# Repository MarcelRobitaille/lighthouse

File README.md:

# Lighthouse

> Lighthouse is a PCB that controls lights in my house.

## Features

- ESP8266 module (works with ESPHome)
- Two constant voltage outputs and two constant current outputs
- Powered from USB-C, barrel, or screw terminal
- Voltage outputs can be powered separately, or from global USB/barrel/screw terminal

It's doesn't have to be for lighting, but any small load you wish to switch remotely.

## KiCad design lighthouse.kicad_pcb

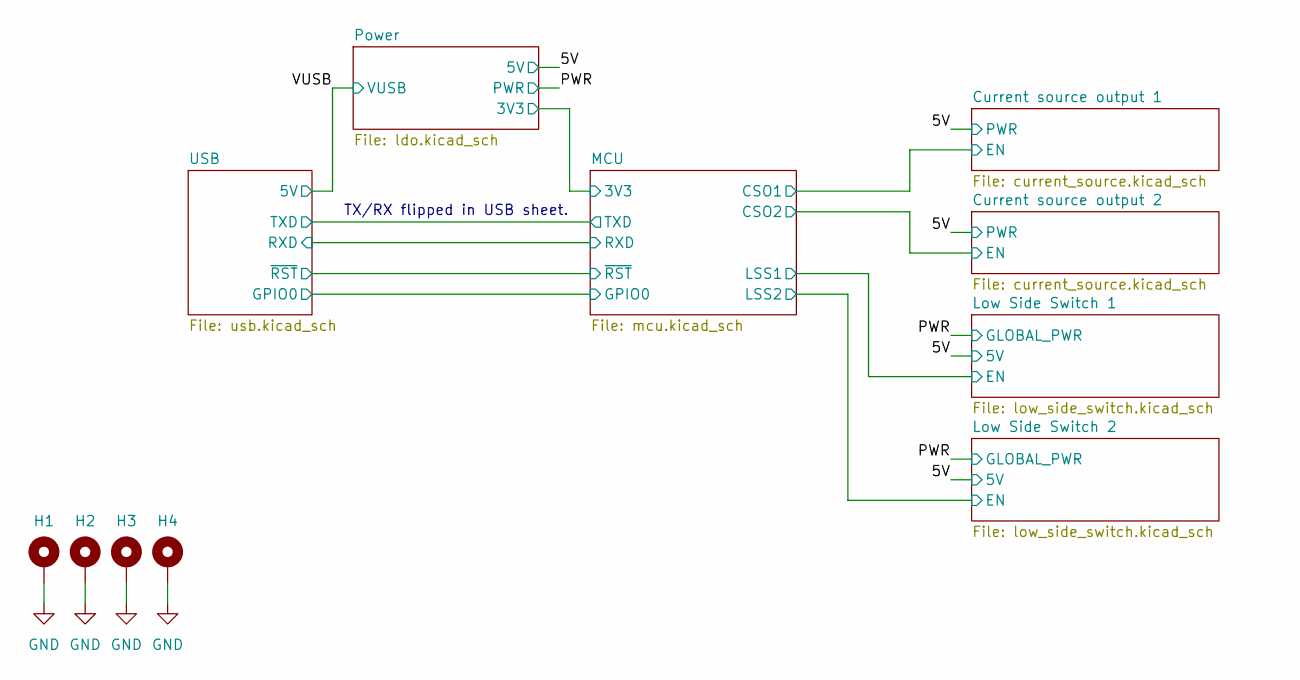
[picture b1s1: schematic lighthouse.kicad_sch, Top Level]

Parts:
H1, H2, H3, H4: MountingHole_Pad; MountingHole_2.2mm_M2_Pad

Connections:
GND: H1.1, H2.1, H3.1, H4.1; also elsewhere on the board

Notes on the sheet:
TX/RX flipped in USB sheet.

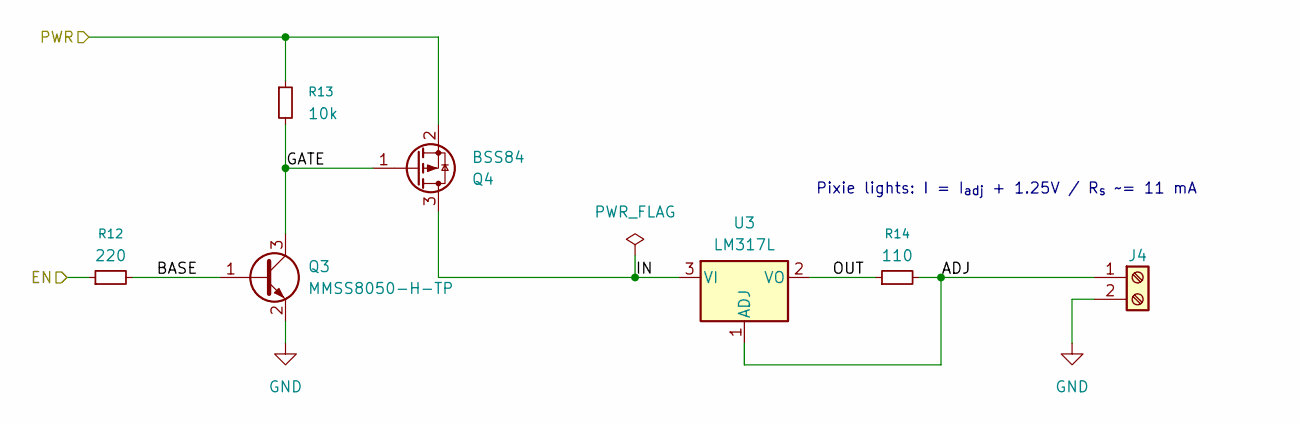
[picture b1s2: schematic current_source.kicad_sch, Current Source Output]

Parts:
J4: TB0010-500-02GR; TerminalBlock_TB0010-500-02GR_1x02_P5.00mm
Q3: MMSS8050-H-TP; SOT-23-3; MPN MMSS8050-H-TP; LCSC Part Number C2891804
Q4: BSS84; SOT-23; MPN BSS84PH6327XTSA2; Digikey Part Number BSS84PH6327XTSA2CT-ND
R12: 220; R_0805_2012Metric; MPN CRCW0805220RJNEA; Mouser Part Number 71-CRCW0805220RJNEA
R13: 10k; R_0805_2012Metric; Tolerance 5 %; MPN CRCW080510K0JNEAC; Mouser Part Number 71-CRCW080510K0JNEAC
R14: 110; R_0805_2012Metric; Tolerance 1%; MPN CRCW0805110RFKEA; Mouser Part Number 71-CRCW0805-110-E3
U3: LM317L; SOT-89-3; MPN LM317LCPK; Mouser Part Number 595-LM317LCPK

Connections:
/5V: Q4.2 (S), R13.1; also elsewhere on the board
/Current source output 2/ADJ: J4.1, R14.2, U3.1 (ADJ)
/Current source output 2/BASE: Q3.1 (B), R12.2
/Current source output 2/GATE: Q3.3 (C), Q4.1 (G), R13.2
/Current source output 2/IN: Q4.3 (D), U3.3 (VI)
/Current source output 2/OUT: R14.1, U3.2 (VO)
/MCU/CSO2: R12.1; also elsewhere on the board
GND: J4.2, Q3.2 (E); also elsewhere on the board

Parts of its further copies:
J7: TB0010-500-02GR; TerminalBlock_TB0010-500-02GR_1x02_P5.00mm
Q5: MMSS8050-H-TP; SOT-23-3; MPN MMSS8050-H-TP; LCSC Part Number C2891804
Q6: BSS84; SOT-23; MPN BSS84PH6327XTSA2; Digikey Part Number BSS84PH6327XTSA2CT-ND
R15: 220; R_0805_2012Metric; MPN CRCW0805220RJNEA; Mouser Part Number 71-CRCW0805220RJNEA
R16: 10k; R_0805_2012Metric; Tolerance 5 %; MPN CRCW080510K0JNEAC; Mouser Part Number 71-CRCW080510K0JNEAC
R17: 110; R_0805_2012Metric; Tolerance 1%; MPN CRCW0805110RFKEA; Mouser Part Number 71-CRCW0805-110-E3
U6: LM317L; SOT-89-3; MPN LM317LCPK; Mouser Part Number 595-LM317LCPK

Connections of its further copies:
/5V: Q6.2 (S), R16.1; also elsewhere on the board
/Current source output 1/ADJ: J7.1, R17.2, U6.1 (ADJ)
/Current source output 1/BASE: Q5.1 (B), R15.2
/Current source output 1/GATE: Q5.3 (C), Q6.1 (G), R16.2
/Current source output 1/IN: Q6.3 (D), U6.3 (VI)
/Current source output 1/OUT: R17.1, U6.2 (VO)
/MCU/CSO1: R15.1; also elsewhere on the board
GND: J7.2, Q5.2 (E); also elsewhere on the board

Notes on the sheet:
Pixie lights: I = I_{adj} + 1.25V / R_{s} ~= 11 mA

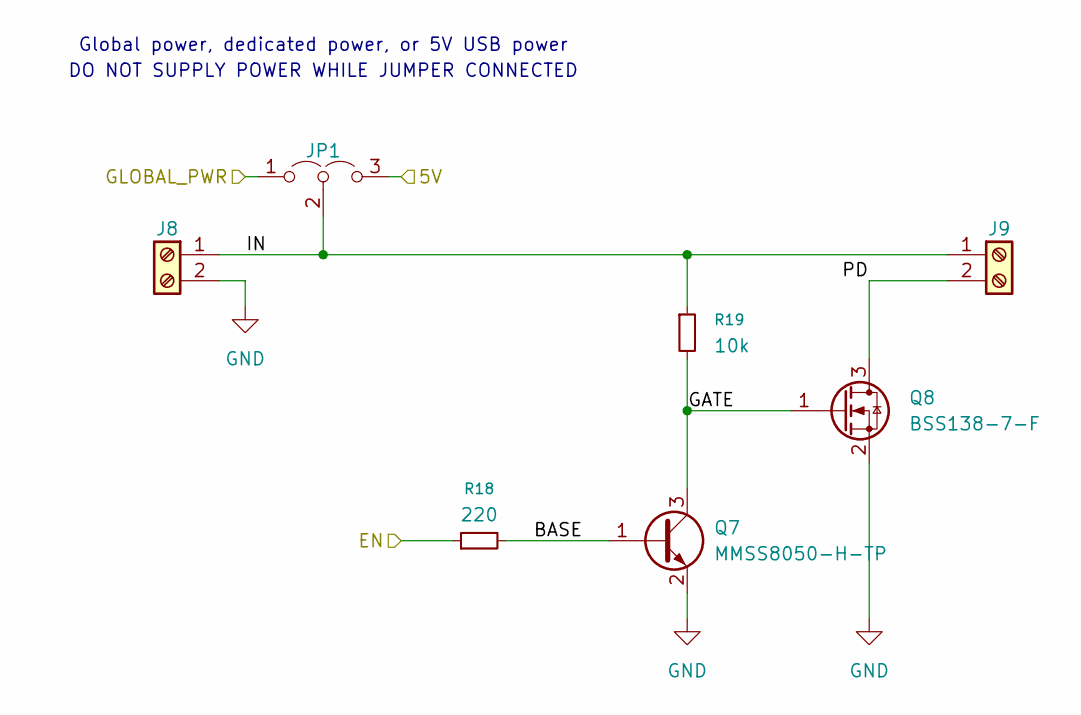
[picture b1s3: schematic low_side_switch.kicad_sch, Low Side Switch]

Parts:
J8, J9: TB0010-500-02GR; TerminalBlock_TB0010-500-02GR_1x02_P5.00mm
JP1: Jumper_3_Open; PinHeader_1x03_P2.54mm_Vertical
Q7: MMSS8050-H-TP; SOT-23-3; MPN MMSS8050-H-TP; LCSC Part Number C2891804
Q8: BSS138-7-F; SOT-23; MPN BSS138-7-F; Digikey Part Numbr BSS138-FDICT-ND
R18: 220; R_0805_2012Metric; MPN CRCW0805220RJNEA; Mouser Part Number 71-CRCW0805220RJNEA
R19: 10k; R_0805_2012Metric; Tolerance 5 %; MPN CRCW080510K0JNEAC; Mouser Part Number 71-CRCW080510K0JNEAC

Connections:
/5V: JP1.3 (B); also elsewhere on the board
/Low Side Switch 2/BASE: Q7.1 (B), R18.2
/Low Side Switch 2/GATE: Q7.3 (C), Q8.1 (G), R19.2
/Low Side Switch 2/IN: J8.1, J9.1, JP1.2 (C), R19.1
/Low Side Switch 2/PD: J9.2, Q8.3 (D)
/MCU/LSS2: R18.1; also elsewhere on the board
/PWR: JP1.1 (A); also elsewhere on the board
GND: J8.2, Q7.2 (E), Q8.2 (S); also elsewhere on the board

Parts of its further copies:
J10, J11: TB0010-500-02GR; TerminalBlock_TB0010-500-02GR_1x02_P5.00mm
JP2: Jumper_3_Open; PinHeader_1x03_P2.54mm_Vertical
Q9: MMSS8050-H-TP; SOT-23-3; MPN MMSS8050-H-TP; LCSC Part Number C2891804
Q10: BSS138-7-F; SOT-23; MPN BSS138-7-F; Digikey Part Numbr BSS138-FDICT-ND
R20: 220; R_0805_2012Metric; MPN CRCW0805220RJNEA; Mouser Part Number 71-CRCW0805220RJNEA
R21: 10k; R_0805_2012Metric; Tolerance 5 %; MPN CRCW080510K0JNEAC; Mouser Part Number 71-CRCW080510K0JNEAC

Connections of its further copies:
/5V: JP2.3 (B); also elsewhere on the board
/Low Side Switch 1/BASE: Q9.1 (B), R20.2
/Low Side Switch 1/GATE: Q9.3 (C), Q10.1 (G), R21.2
/Low Side Switch 1/IN: J10.1, J11.1, JP2.2 (C), R21.1
/Low Side Switch 1/PD: J11.2, Q10.3 (D)
/MCU/LSS1: R20.1; also elsewhere on the board
/PWR: JP2.1 (A); also elsewhere on the board
GND: J10.2, Q9.2 (E), Q10.2 (S); also elsewhere on the board

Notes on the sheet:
Global power, dedicated power, or 5V USB power
DO NOT SUPPLY POWER WHILE JUMPER CONNECTED

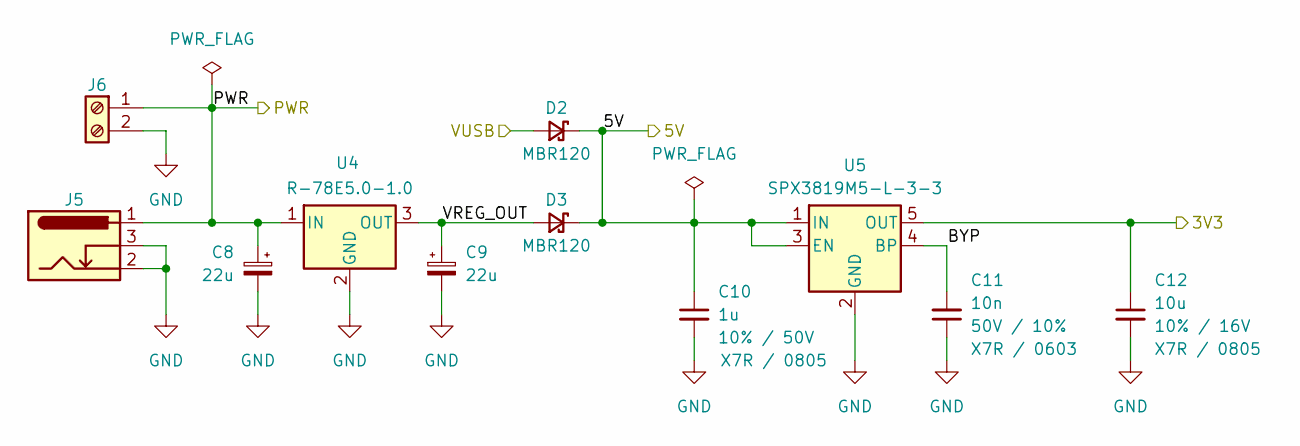
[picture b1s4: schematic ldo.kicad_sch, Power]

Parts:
C8, C9: 22u; C_Radial_D5.0mm_H5.0mm_P2.00mm
C10: 1u; C_0805_2012Metric; Tolerance 10%; Rated Voltage 50V; MPN CC0805KKX7R9BB105; LCSC Part Number C91185
C11: 10n; C_0603_1608Metric; Rated Voltage 50V; Tolerance 10%; MPN CC0603KRX7R9BB103; LCSC Part Number C100042
C12: 10u; C_0805_2012Metric; Rated Voltage 16V; Tolerance 10%; MPN CL21A106KOQNNNE; Mouser Part Number 187-CL21A106KOQNNNE
D2, D3: MBR120; D_SOD-123F; MPN MBR120ESFT1G; Mouser Part Number 863-MBR120ESFT1G
J5: 694106301002; BarrelJack_Wuerth_6941xx301002; MPN 694106301002; Digikey Part Number 732-5930-ND
J6: TB0010-500-02GR; TerminalBlock_TB0010-500-02GR_1x02_P5.00mm
U4: R-78E5.0-1.0; Converter_DCDC_RECOM_R-78E-0.5_THT; MPN R-78E5.0-1.0; Mouser Part Number 919-R-78E5.0-1.0
U5: SPX3819M5-L-3-3; SOT-23-5; MPN SPX3819M5-L-3-3/TR; LCSC Part Number C9055

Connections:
/5V: C10.1, D2.1 (K), D3.1 (K), U5.1 (IN), U5.3 (EN); also elsewhere on the board
/MCU/3V3: C12.1, U5.5 (OUT); also elsewhere on the board
/PWR: C8.1, J5.1, J6.1, U4.1 (IN); also elsewhere on the board
/Power/BYP: C11.2, U5.4 (BP)
/Power/VREG_OUT: C9.1, D3.2 (A), U4.3 (OUT)
/VUSB: D2.2 (A); also elsewhere on the board
GND: C8.2, C9.2, C10.2, C11.1, C12.2, J5.2, J5.3, J6.2, U4.2 (GND), U5.2 (GND); also elsewhere on the board

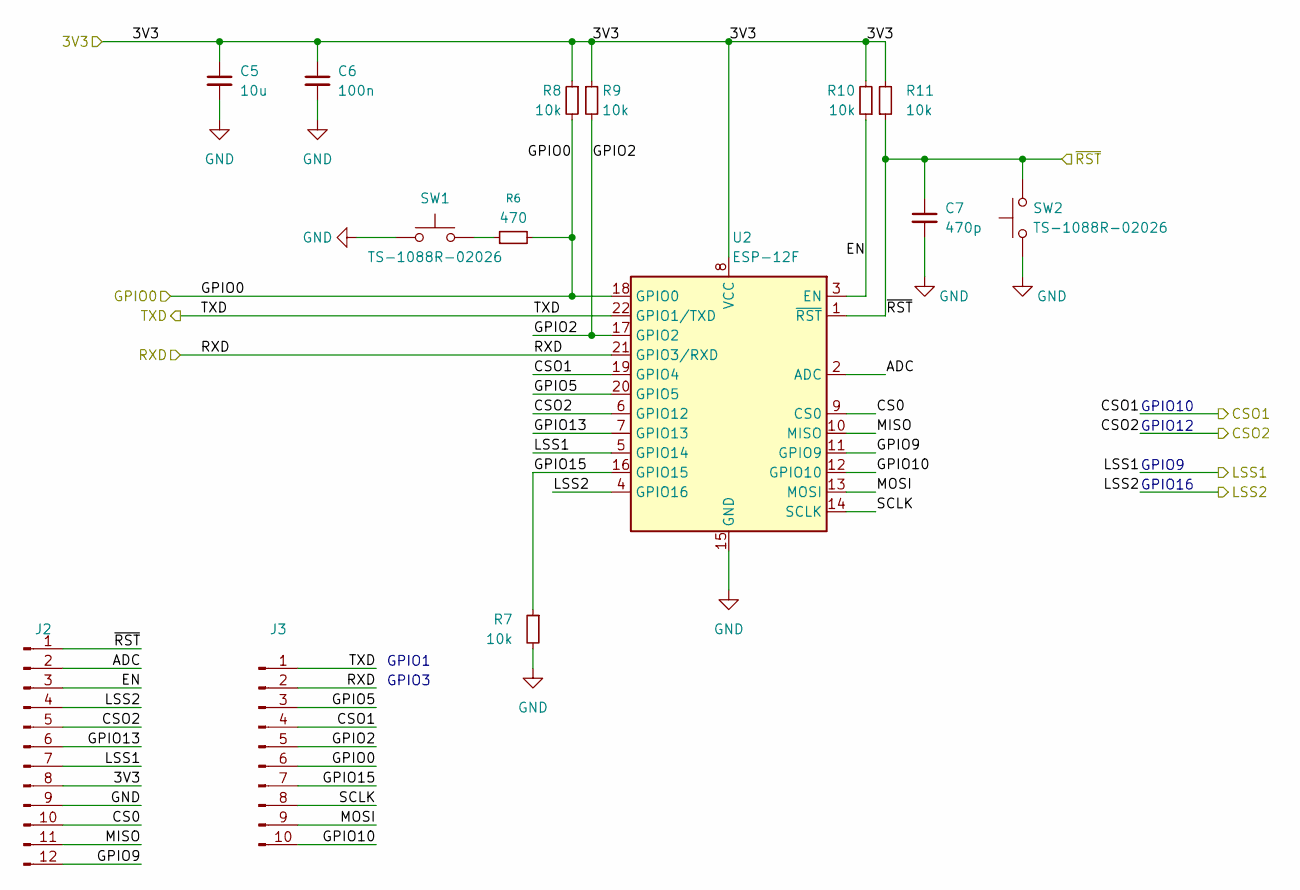
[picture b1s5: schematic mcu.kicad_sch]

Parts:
C5: 10u; C_0805_2012Metric; Rated Voltage 16V; Tolerance 10%; MPN CL21A106KOQNNNE; Mouser Part Number 187-CL21A106KOQNNNE
C6: 100n; C_0805_2012Metric; Rated Voltage 50V; Tolerance 10%; MPN 0805B104K500NT; LCSC Part Number C38141
C7: 470p; C_0805_2012Metric; MPN 885012007038; Mouser Part Number 710-885012007038
J2: Conn_01x05_Pin; PinHeader_1x12_P2.54mm_Vertical
J3: Conn_01x10_Pin; PinHeader_1x10_P2.54mm_Vertical
R6: 470; R_0805_2012Metric; Tolerance 1%; MPN CRCW0805470RFKEA; Mouser Part Number 71-CRCW0805-470-E3
R7, R8, R9, R10, R11: 10k; R_0805_2012Metric; Tolerance 5 %; MPN CRCW080510K0JNEAC; Mouser Part Number 71-CRCW080510K0JNEAC
SW1, SW2: TS-1088R-02026; TS-1088R-02026_SW_SMD_3x4mm; MPN TS-1088R-02026; LCSC Part Number C455280
U2: ESP-12F; ESP-12E; MPN ESP-12F(ESP8266MOD); LCSC Part Number C82891

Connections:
/MCU/3V3: C5.1, C6.1, J2.8, R8.1, R9.1, R10.2, R11.2, U2.8 (VCC); also elsewhere on the board
/MCU/ADC: J2.2, U2.2 (ADC)
/MCU/CS0: J2.10, U2.9 (CS0)
/MCU/CSO1: J3.4, U2.19 (GPIO4); also elsewhere on the board
/MCU/CSO2: J2.5, U2.6 (GPIO12); also elsewhere on the board
/MCU/EN: J2.3, R10.1, U2.3 (EN)
/MCU/GPIO0: J3.6, R6.2, R8.2, U2.18 (GPIO0); also elsewhere on the board
/MCU/GPIO2: J3.5, R9.2, U2.17 (GPIO2)
/MCU/GPIO5: J3.3, U2.20 (GPIO5)
/MCU/GPIO9: J2.12, U2.11 (GPIO9)
/MCU/GPIO10: J3.10, U2.12 (GPIO10)
/MCU/GPIO13: J2.6, U2.7 (GPIO13)
/MCU/GPIO15: J3.7, R7.1, U2.16 (GPIO15)
/MCU/LSS1: J2.7, U2.5 (GPIO14); also elsewhere on the board
/MCU/LSS2: J2.4, U2.4 (GPIO16); also elsewhere on the board
/MCU/MISO: J2.11, U2.10 (MISO)
/MCU/MOSI: J3.9, U2.13 (MOSI)
/MCU/RXD: J3.2, U2.21 (GPIO3/RXD); also elsewhere on the board
/MCU/SCLK: J3.8, U2.14 (SCLK)
/MCU/TXD: J3.1, U2.22 (GPIO1/TXD); also elsewhere on the board
/MCU/~RST: C7.1, J2.1, R11.1, SW2.2, U2.1 (~RST); also elsewhere on the board
GND: C5.2, C6.2, C7.2, J2.9, R7.2, SW1.2, SW2.1, U2.15 (GND); also elsewhere on the board
unnamed: R6.1, SW1.1

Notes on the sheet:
GPIO16
GPIO1
GPIO10
GPIO12
GPIO3
GPIO9

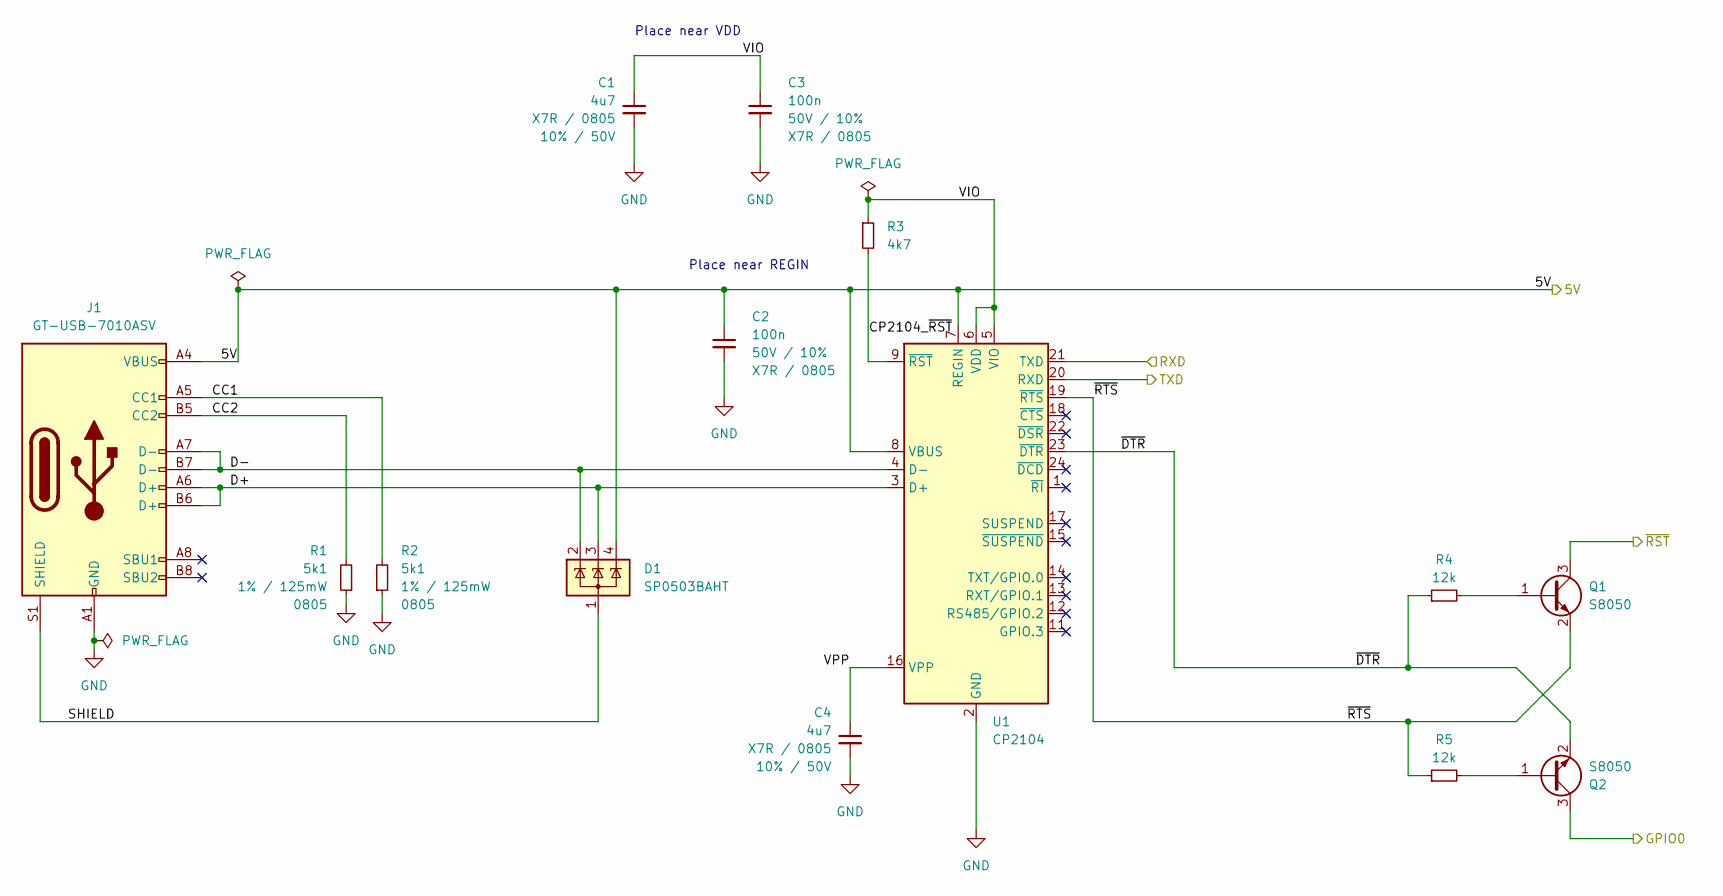
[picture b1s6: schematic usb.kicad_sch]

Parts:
C1, C4: 4u7; C_0805_2012Metric; Rated Voltage 50V; Tolerance 10%; MPN CL21A475KBQNNNE; LCSC Part Number C98192
C2, C3: 100n; C_0805_2012Metric; Rated Voltage 50V; Tolerance 10%; MPN 0805B104K500NT; LCSC Part Number C38141
D1: SP0503BAHT; SOT-143; MPN SP0503BAHTG; LCSC Part Number C7074
J1: GT-USB-7010ASV; USB_C_Receptacle_G-Switch_GT-USB-7010ASV; MPN G-Switch; LCSC Part Number C2988369
Q1, Q2: S8050; SOT-23-3; MPN MMSS8050-L-TP; Mouser Part Number 833-MMSS8050-L-TP
R1, R2: 5k1; R_0805_2012Metric; Tolerance 1%; MPN CRCW08055K10FKEAC; Mouser Part Number 71-CRCW08055K10FKEAC
R3: 4k7; R_0805_2012Metric; Tolerance 1%; MPN CR0805-FX-4701ELF; Mouser Part Number 652-CR0805FX-4701ELF
R4, R5: 12k; R_0805_2012Metric; Tolerance 1%; MPN CRCW080512K0JNEA; Mouser Part Number 71-CRCW080512K0JNEA
U1: CP2104; QFN-24-1EP_4x4mm_P0.5mm_EP2.6x2.6mm; MPN CP2104-F03-GMR; LCSC Part Number C47742

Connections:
/MCU/GPIO0: Q2.3 (C); also elsewhere on the board
/MCU/RXD: U1.21 (TXD); also elsewhere on the board
/MCU/TXD: U1.20 (RXD); also elsewhere on the board
/MCU/~RST: Q1.3 (C); also elsewhere on the board
/USB/CC1: J1.A5 (CC1), R2.2
/USB/CC2: J1.B5 (CC2), R1.2
/USB/CP2104_~RST: R3.2, U1.9 (~RST)
/USB/D+: D1.3 (K), J1.A6 (D+), J1.B6 (D+), U1.3 (D+)
/USB/D-: D1.2 (K), J1.A7 (D-), J1.B7 (D-), U1.4 (D-)
/USB/SHIELD: D1.1 (A), J1.S1 (SHIELD)
/USB/VIO: C1.1, C3.1, R3.1, U1.5 (VIO), U1.6 (VDD)
/USB/VPP: C4.1, U1.16 (VPP)
/USB/~DTR: Q2.2 (E), R4.1, U1.23 (~DTR)
/USB/~RTS: Q1.2 (E), R5.1, U1.19 (~RTS)
/VUSB: C2.1, D1.4 (K), J1.A4 (VBUS), J1.A9 (VBUS), J1.B4 (VBUS), J1.B9 (VBUS), U1.7 (REGIN), U1.8 (VBUS); also elsewhere on the board
GND: C1.2, C2.2, C3.2, C4.2, J1.A1 (GND), J1.A12 (GND), J1.B1 (GND), J1.B12 (GND), R1.1, R2.1, U1.2 (GND), U1.25 (GND); also elsewhere on the board
unnamed: Q1.1 (B), R4.2
unnamed: Q2.1 (B), R5.2

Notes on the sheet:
Place near VDD
Place near REGIN

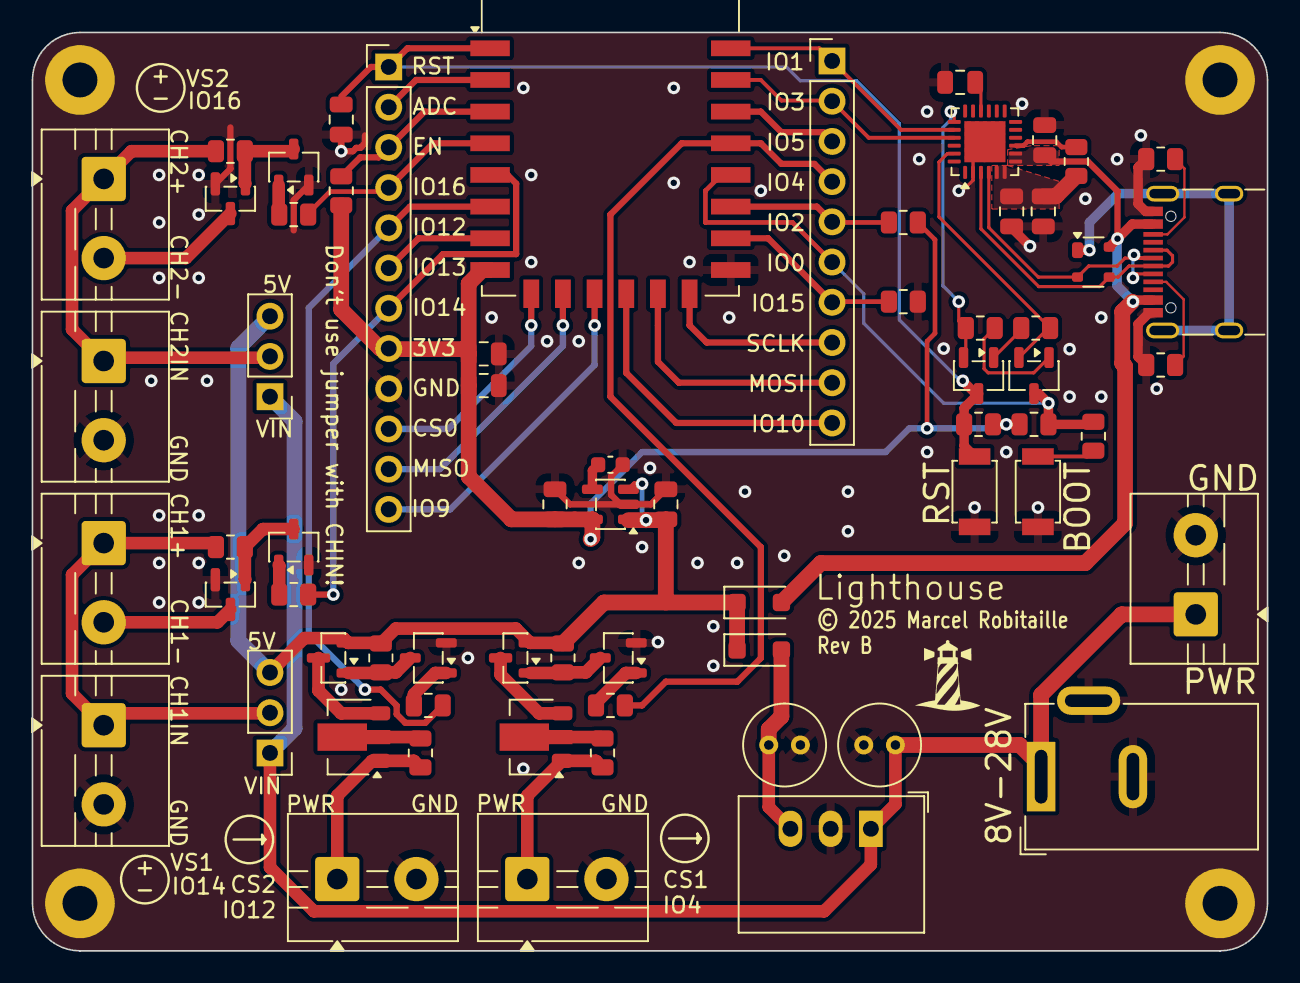
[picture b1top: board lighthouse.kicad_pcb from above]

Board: 2 copper layers, 78.0 x 58.0 mm, 71 parts (0 on the bottom side), 58 nets.

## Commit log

2025-09-15 Update to kicad 9
2025-09-15 Fix hardware flow control transistor pinouts
2025-09-15 Fix using same GPIO for epd D/C and boot
2025-09-15 Update reference designators to single digit
    Fits on the silk better
2025-09-15 Update layout and routing
2025-11-10 Lighthouse
2025-11-12 Ignore fabrication artifacts
2025-11-12 Ignore additional footprint
2025-11-12 Renamifications
2025-11-12 README
2025-11-12 Termianl block 3d view
2025-11-12 Remove lighthouse logo from readme
2025-11-16 Add component attributes
2025-12-01 Correct unusable FLASH SPI pins

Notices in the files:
lighthouse.kicad_pcb:
© 2025 Marcel Robitaille
